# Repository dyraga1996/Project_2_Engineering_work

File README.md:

# Project_2_Engineering_work
Design and implementation of an access control system using RFID technology. 
The system will consist of three components: 
- an electronic device
- a program written in C++ language for the microcontroller
- a web server on which the Internet application and the MySQL database will be located.

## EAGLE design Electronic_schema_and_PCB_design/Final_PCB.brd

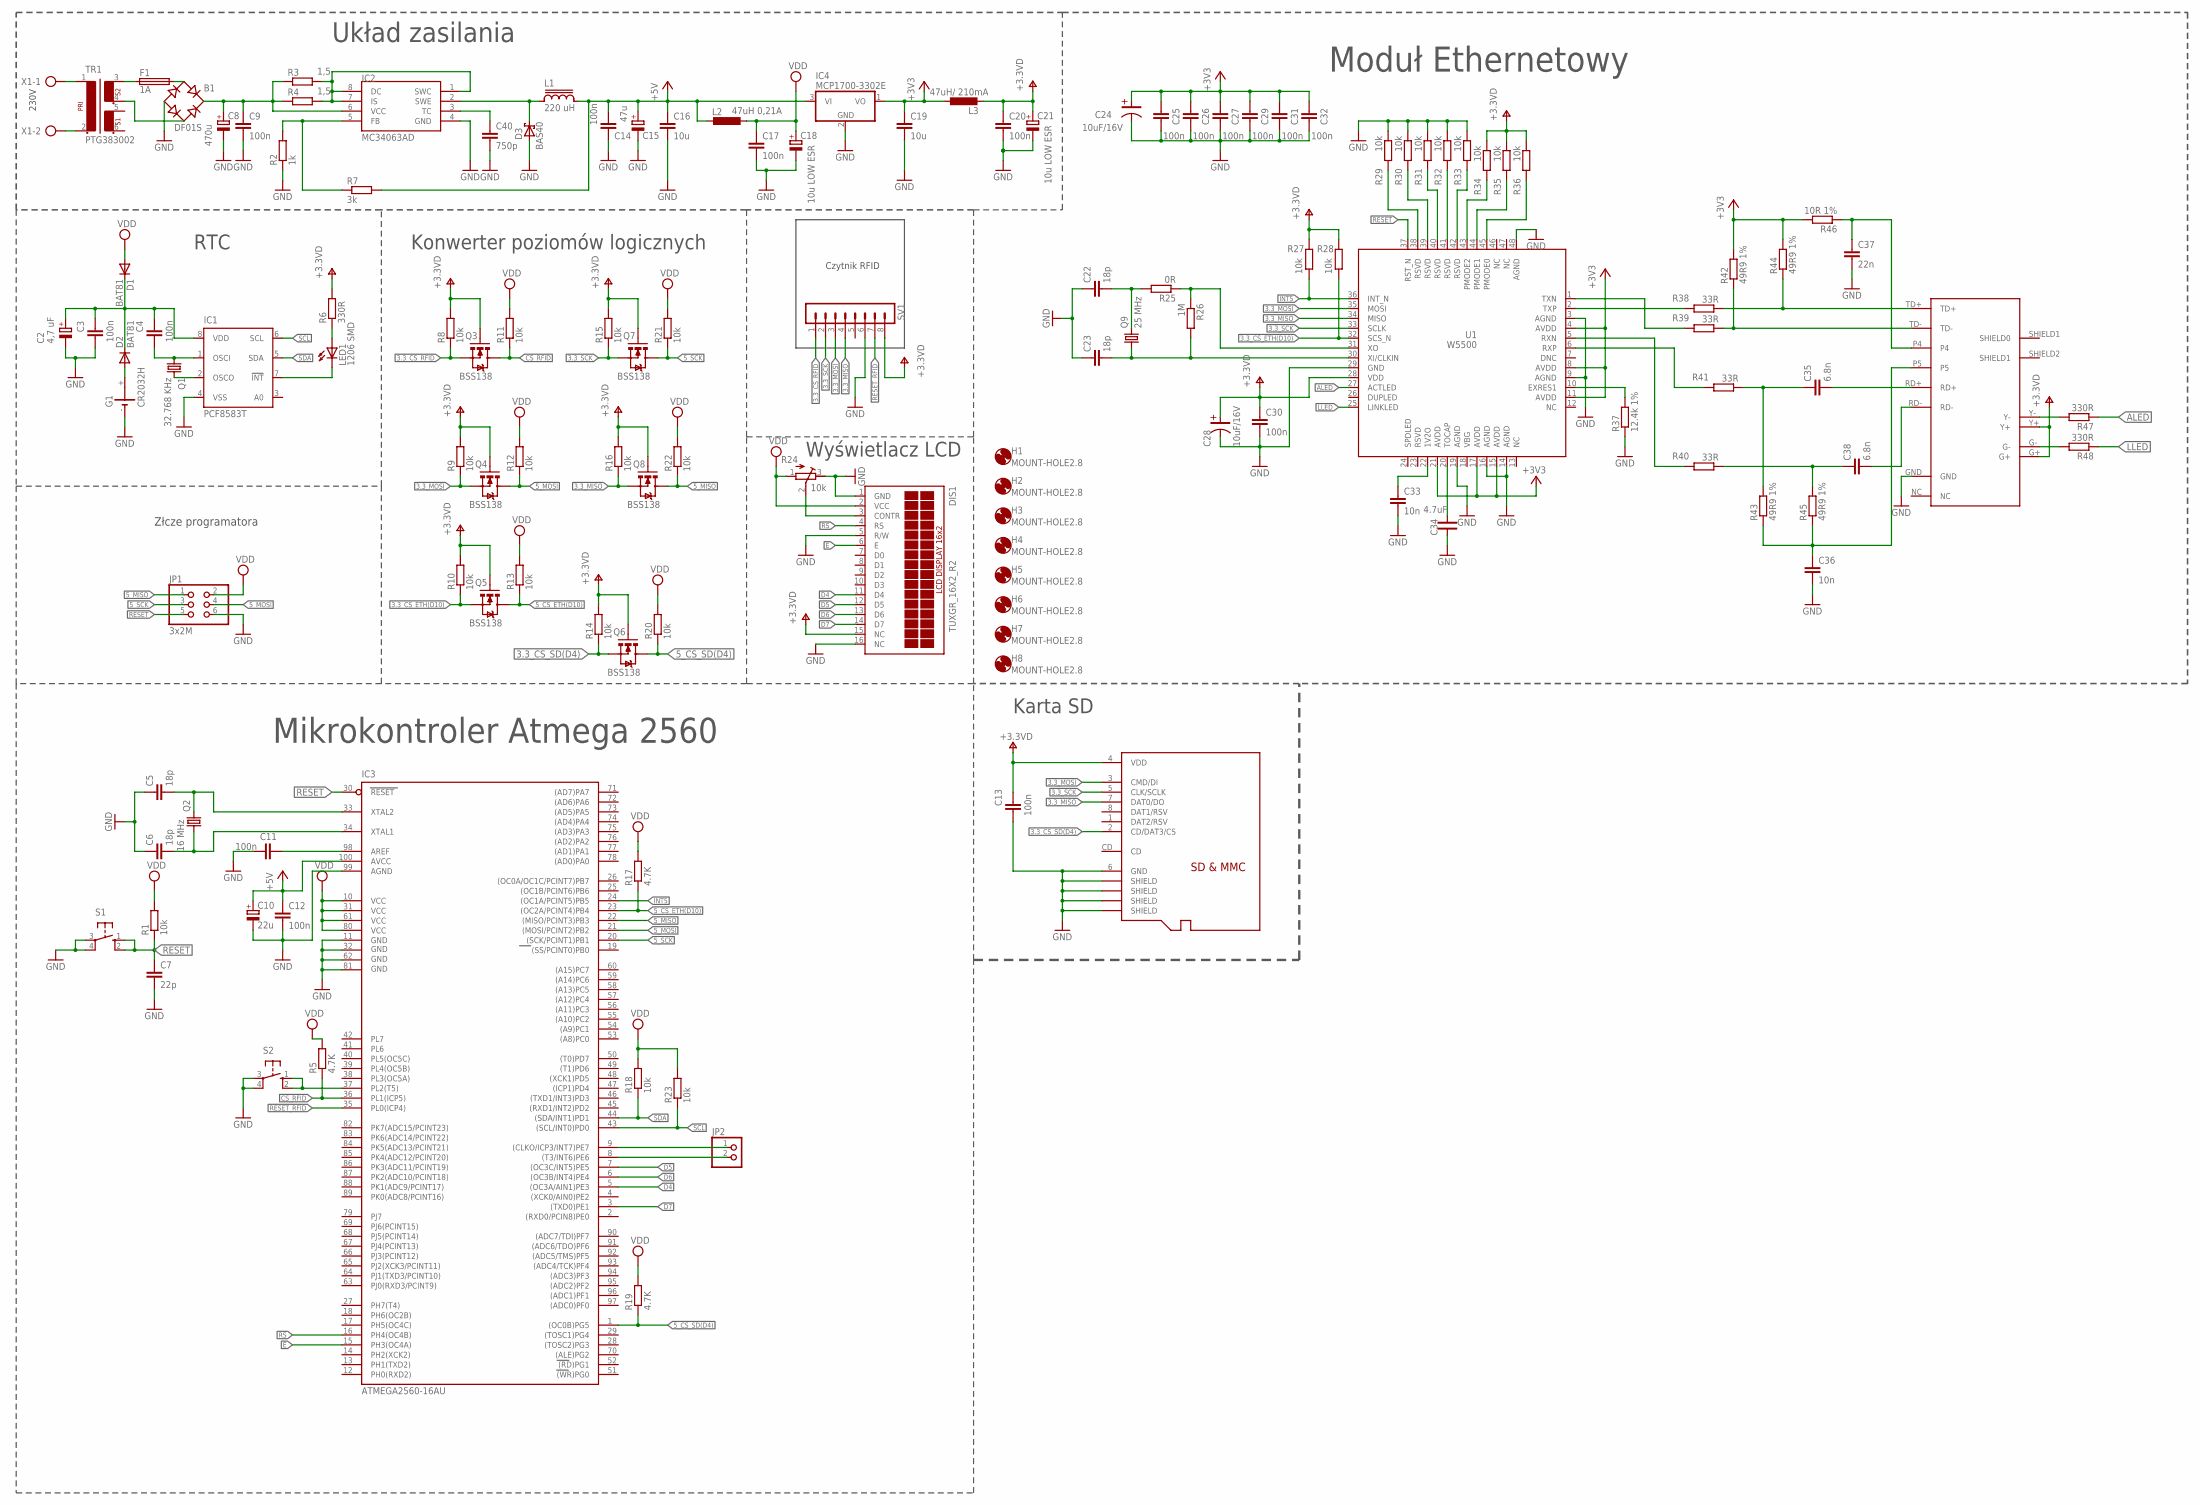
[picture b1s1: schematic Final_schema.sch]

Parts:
B1: DF01S; DB
C2: 4,7 uF; UD-5X5,8_NICHICON
C3, C4, C9, C12, C13, C14, C25, C26, C27, C29, C31, C32: 100n; C0603
C5, C6, C22, C23: 18p; C0603
C7: 22p; C0603
C8: 470u; E7,5-16
C10: 22u; UD-5X5,8_NICHICON
C11: 100n; C0603-ROUND
C15: 47u; 153CLV-0505
C16, C19: 10u; C0603
C17, C20, C30: 100n; C0603K
C18, C21: 10u LOW ESR; E5-10,5
C24, C28: 10uF/16V; C-3216(TANTAL)
C33, C36: 10n; C0603
C34: 4.7uF; C-2012
C35, C38: 6.8n; C0603
C37: 22n; C0603
C40: 750p; C0603K
D1, D2: BAT81; DO34-7
D3: BAS40; SOT23
DIS1: TUXGR_16X2_R2
F1: 1A; GSH15
G1: CR2032H
H1, H2, H3, H4, H5, H6, H7, H8: MOUNT-HOLE2.8; 2,8
IC1: PCF8583T; SO8-7_5
IC2: MC34063AD; SOIC8
IC3: ATMEGA2560-16AU; TQFP100
IC4: MCP1700-3302E; TO92
JP1: 3x2M; 2X03
JP2: D5; 1X02
L1: 220 uH; CD54
L2: 47uH 0,21A; L1812
L3: 47uH/ 210mA; L1812
LED1: 1206 SMD; LED_1206
Q1: 32.768 KHz; TC26H
Q2: 16 MHz; HC49/S
Q3, Q4, Q5, Q6, Q7, Q8: BSS138; SOT23-3
Q9: 25 MHz; HC49/S
R1, R8, R9, R10, R11, R12, R13, R14, R15, R16, R18, R20, R21, R22, R23, R27, R28, R29, R30, R31, R32, R33, R34, R35, R36: 10k; R0603
R2: 1k; R0603
R3, R4: 1,5; 0411/15
R5, R17, R19: 4.7K; R0603
R6, R47, R48: 330R; R0603
R7: 3k; R0603
R24: 10k; RTRIM4G/J
R25: 0R; R0603
R26: 1M; R0603
R37: 12.4k 1%; R0603
R38, R39, R40, R41: 33R; R0603
R42, R43, R44, R45: 49R9 1%; R0603
R46: 10R 1%; R0603
S1: SW3; B3F-10XX
S2: SW; B3F-10XX
SV1: RC522; MA08-1
TR1: PTG383002; VR12
U1: W5500
U$1: HR911105A; RJ45
U$2: MICROSD; C12075
X1: 230V; AK500/2-H

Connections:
3.3_CS_ETH(D10): Q5.2 (S), R10.1, R28.1, U1.32 (SCS_N)
3.3_CS_RFID: Q3.2 (S), R8.1, SV1.1
3.3_CS_SD(D4): Q6.2 (S), R14.1, U$2.2 (CD/DAT3/CS)
3.3_MISO: Q8.2 (S), R16.1, SV1.4, U1.34 (MISO), U$2.7 (DAT0/DO)
3.3_MOSI: Q4.2 (S), R9.1, SV1.3, U1.35 (MOSI), U$2.3 (CMD/DI)
3.3_SCK: Q7.2 (S), R15.1, SV1.2, U1.33 (SCLK), U$2.5 (CLK/SCLK)
5_CS_ETH(D10): IC3.23 ((OC2A/PCINT4)PB4), Q5.3 (D), R13.1, R17.1
5_CS_SD(D4): IC3.1 ((OC0B)PG5), Q6.3 (D), R19.1, R20.1
5_MISO: IC3.22 ((MISO/PCINT3)PB3), JP1.1, Q8.3 (D), R22.1
5_MOSI: IC3.21 ((MOSI/PCINT2)PB2), JP1.4, Q4.3 (D), R12.1
5_SCK: IC3.20 ((SCK/PCINT1)PB1), JP1.3, Q7.3 (D), R21.1
+3V3: C19.1, C24.1, C25.1, C26.1, C27.1, C29.1, C31.1, C32.1, IC4.1 (VO), L3.1, R42.2, R44.2, R46.2, U1.4 (AVDD), U1.8 (AVDD), U1.11 (AVDD), U1.15 (AVDD), U1.17 (AVDD), U1.21 (AVDD)
+5V: C10.+, C12.1, C14.1, C15.+, C16.1, IC3.100 (AVCC), IC4.3 (VI), L1.2, L2.2, R7.2
ALED: R47.1, U1.27 (ACTLED)
AREF: C11.1, IC3.98 (AREF)
CS_RFID: IC3.36 (PL1(ICP5)), Q3.3 (D), R5.1, R11.1
D4: DIS1.11 (D4), IC3.5 ((OC3A/AIN1)PE3)
D5: DIS1.12 (D5), IC3.7 ((OC3C/INT5)PE5)
D6: DIS1.13 (D6), IC3.6 ((OC3B/INT4)PE4)
D7: DIS1.14 (D7), IC3.3 ((TXD0)PE1)
E: DIS1.6 (E), IC3.15 (PH3(OC4A))
GND: B1.-, C2.-, C3.2, C5.1, C6.1, C7.2, C8.-, C9.2, C10.-, C11.2, C12.2, C13.2, C14.2, C15.-, C16.2, C17.2, C18.-, C19.2, C20.2, C21.-, C22.1, C23.1, C24.2, C25.2, C26.2, C27.2, C28.2, C29.2, C30.2, C31.2, C32.2, C33.2, C34.P$1, C36.2, C37.2, C40.2, D3.1 (A), DIS1.1 (GND), DIS1.5 (R/W), DIS1.16 (NC), G1.-, IC1.4 (VSS), IC2.4 (GND), IC3.11 (GND), IC3.32 (GND1), IC3.62 (GND2), IC3.81 (GND3), IC3.99 (AGND), IC4.2 (GND), JP1.6, R2.1, R24.3 (E), R29.2, R30.2, R31.2, R32.2, R33.2, R37.1, S1.3, S1.4 (P1), S2.3, S2.4 (P1), SV1.6, U1.3 (AGND), U1.9 (AGND), U1.14 (AGND), U1.16 (AGND), U1.19 (AGND), U1.29 (GND), U1.48 (AGND), U$1.GND, U$2.6 (GND), U$2.GND@1 (SHIELD), U$2.GND@2 (SHIELD), U$2.GND@3 (SHIELD), U$2.GND@4 (SHIELD)
INT5: IC3.24 ((OC1A/PCINT5)PB5), R27.1, U1.36 (INT_N)
LLED: R48.1, U1.25 (LINKLED)
unnamed: IC1.7 (!INT), LED1.C
unnamed: R29.1, U1.38 (RSVD)
unnamed: IC2.5 (FB), R2.2, R7.1
unnamed: IC2.1 (SWC), IC2.7 (IS), IC2.8 (DC), R3.2, R4.2
unnamed: D3.3 (C), IC2.2 (SWE), L1.1
unnamed: C40.1, IC2.3 (TC)
unnamed: TR1.1, X1.1
unnamed: TR1.2, X1.2
unnamed: B1.AC1, F1.2
unnamed: B1.AC2, TR1.4 (5)
unnamed: F1.1, TR1.3 (6)
unnamed: B1.+, C8.+, C9.1, IC2.6 (VCC), R3.1, R4.1
unnamed: R47.2, U$1.Y-
unnamed: R41.2, U1.6 (RXP)
unnamed: DIS1.3 (CONTR), R24.2 (S)
unnamed: R30.1, U1.39 (RSVD)
unnamed: R31.1, U1.40 (RSVD)
unnamed: C22.2, Q9.2, R25.2
unnamed: IC3.9 ((CLKO/ICP3/INT7)PE7), JP2.1
unnamed: IC3.8 ((T3/INT6)PE6), JP2.2
unnamed: R48.2, U$1.G-
unnamed: IC3.37 (PL2(T5)), S2.1 (S), S2.2 (S1)
unnamed: C4.2, IC1.1 (OSCI), Q1.1
unnamed: IC1.2 (OSCO), Q1.2
unnamed: D2.A, G1.+
unnamed: C2.+, C3.1, C4.1, D1.C, D2.C, IC1.8 (VDD)
unnamed: R32.1, U1.41 (RSVD)
unnamed: R33.1, U1.42 (RSVD)
unnamed: R34.1, U1.43 (PMODE2)
unnamed: R35.1, U1.44 (PMODE1)
unnamed: R36.1, U1.45 (PMODE0)
unnamed: C34.P$2, U1.20 (TOCAP)
unnamed: C33.1, U1.22 (1V2O)
unnamed: R37.2, U1.10 (EXRES1)
unnamed: C37.1, R46.1, U$1.P4
unnamed: C35.2, U$1.RD+
unnamed: C38.2, U$1.RD-
unnamed: C36.1, R43.1, R45.1, U$1.P5
unnamed: LED1.A, R6.1
unnamed: R25.1, R26.1, U1.31 (XO)
unnamed: R40.2, U1.5 (RXN)
unnamed: R38.2, U1.2 (TXP)
unnamed: R39.2, U1.1 (TXN)
unnamed: C23.2, Q9.1, R26.2, U1.30 (XI/CLKIN)
RESET: C7.1, IC3.30 (RESET), JP1.5, R1.1, S1.1 (S), S1.2 (S1), U1.37 (RST_N)
RESET_RFID: IC3.35 (PL0(ICP4)), SV1.7
RS: DIS1.4 (RS), IC3.16 (PH4(OC4B))
RXN: C38.1, R40.1, R45.2
RXP: C35.1, R41.1, R43.2
SCL: IC1.6 (SCL), IC3.43 ((SCL/INT0)PD0), R23.1
SDA: IC1.5 (SDA), IC3.44 ((SDA/INT1)PD1), R18.1
TXN: R39.1, R42.1, U$1.TD-
TXP: R38.1, R44.1, U$1.TD+
V+: C13.1, C20.1, C21.+, C28.1, C30.1, DIS1.15 (NC), L3.2, Q3.1 (G), Q4.1 (G), Q5.1 (G), Q6.1 (G), Q7.1 (G), Q8.1 (G), R6.2, R8.2, R9.2, R10.2, R14.2, R15.2, R16.2, R27.2, R28.2, R34.2, R35.2, R36.2, SV1.8, U1.28 (VDD), U$1.G+, U$1.Y+, U$2.4 (VDD)
VDD: C17.1, C18.+, D1.A, DIS1.2 (VCC), IC3.10 (VCC), IC3.31 (VCC1), IC3.61 (VCC2), IC3.80 (VCC3), JP1.2, L2.1, R1.2, R5.2, R11.2, R12.2, R13.2, R17.2, R18.2, R19.2, R20.2, R21.2, R22.2, R23.2, R24.1 (A)
XTAL1: C6.2, IC3.34 (XTAL1), Q2.1
XTAL2: C5.2, IC3.33 (XTAL2), Q2.2

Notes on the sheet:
230V
Układ zasilania
Czytnik RFID
Wyświetlacz LCD
Konwerter poziomów logicznych
RTC
Karta SD
Złcze programatora
Moduł Ethernetowy
Mikrokontroler Atmega 2560

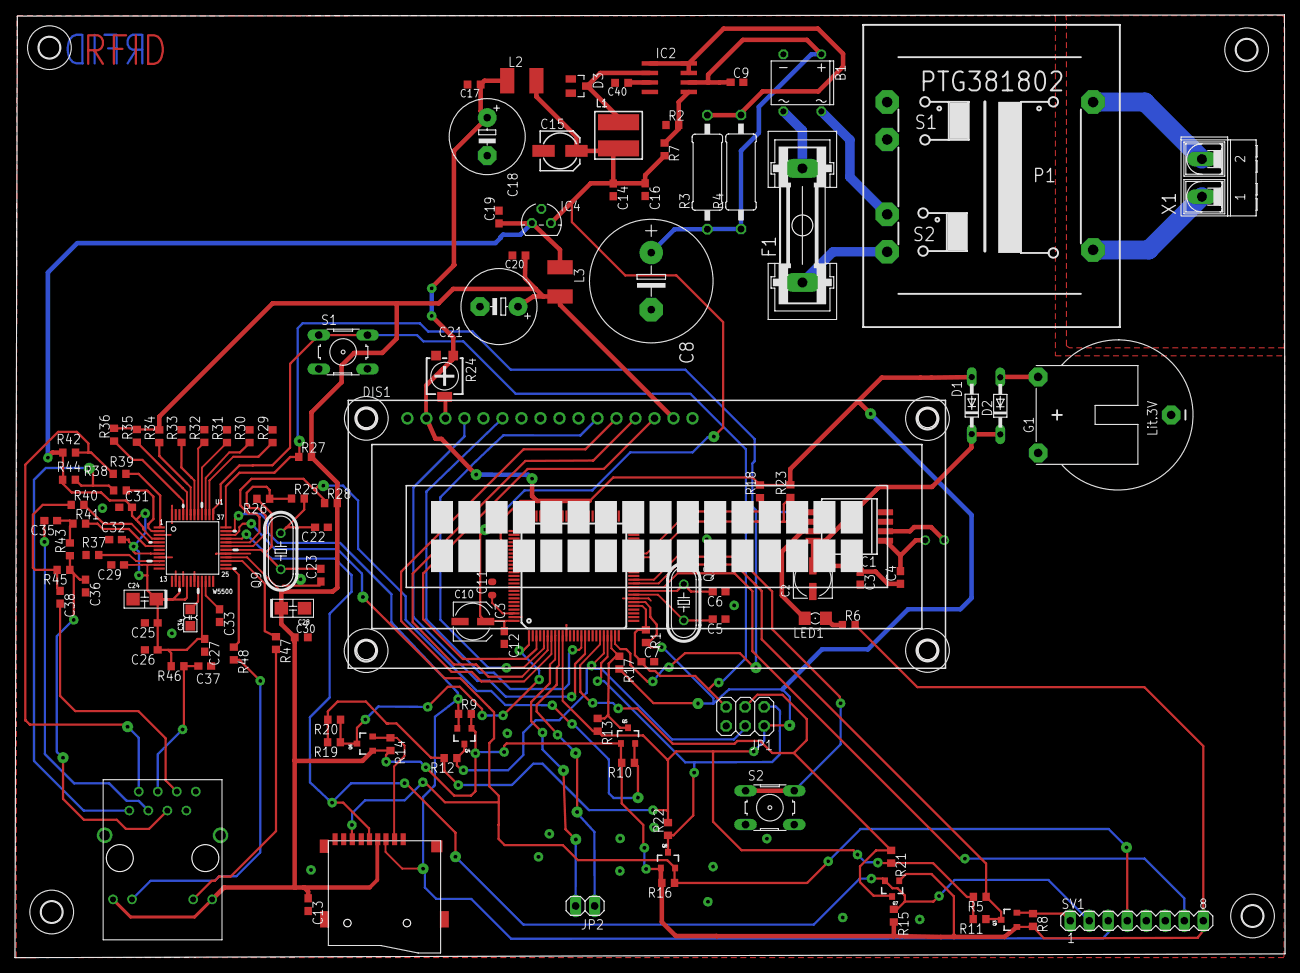
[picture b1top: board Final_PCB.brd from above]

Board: 2 copper layers, 169.7 x 126.0 mm, 128 parts (1 on the bottom side), 81 nets.

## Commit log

2020-02-16 Final schema
2020-02-16 final board PCB
2020-02-16 Final version microcontroller_program
2020-02-16 Ignore files
2020-02-16 add new ignore files
2020-02-16 edit ignore files
2020-02-16 Final version internet application with MySQL database
2020-02-16 Bump symfony/phpunit-bridge in /Internet_application
    Bumps [symfony/phpunit-bridge](https://github.com/symfony/phpunit-bridge) from 3.4.21 to 3.4.26.
    - [Release notes](https://github.com/symfony/phpunit-bridge/releases)
    - [Changelog](https://github.com/symfony/phpunit-bridge/blob/master/CHANGELOG.md)
    - [Commits](https://github.com/symfony/phpunit-bridge/compare/v3.4.21...v3.4.26)
2022-03-26 Bump twig/twig from 1.37.1 to 1.38.0 in /Internet_application
    Bumps [twig/twig](https://github.com/twigphp/Twig) from 1.37.1 to 1.38.0.
    - [Release notes](https://github.com/twigphp/Twig/releases)
    - [Changelog](https://github.com/twigphp/Twig/blob/v1.38.0/CHANGELOG)
    - [Commits](https://github.com/twigphp/Twig/compare/v1.37.1...v1.38.0)
    ---
    updated-dependencies:
2022-09-30 Bump twig/twig from 1.37.1 to 1.42.5 in /Internet_application
    Bumps [twig/twig](https://github.com/twigphp/Twig) from 1.37.1 to 1.42.5.
    - [Release notes](https://github.com/twigphp/Twig/releases)
    - [Changelog](https://github.com/twigphp/Twig/blob/v1.42.5/CHANGELOG)
    - [Commits](https://github.com/twigphp/Twig/compare/v1.37.1...v1.42.5)
    ---
    updated-dependencies:
2023-02-01 Bump symfony/symfony from 3.4.21 to 3.4.49 in /Internet_application
    Bumps [symfony/symfony](https://github.com/symfony/symfony) from 3.4.21 to 3.4.49.
    - [Release notes](https://github.com/symfony/symfony/releases)
    - [Changelog](https://github.com/symfony/symfony/blob/v3.4.49/CHANGELOG-3.4.md)
    - [Commits](https://github.com/symfony/symfony/compare/v3.4.21...v3.4.49)
    ---
    updated-dependencies:

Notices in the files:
parts and their libraries:
inductor-sumida: Copyright (C) 2008, Bob Starr
